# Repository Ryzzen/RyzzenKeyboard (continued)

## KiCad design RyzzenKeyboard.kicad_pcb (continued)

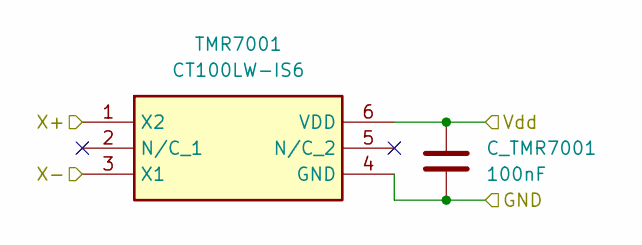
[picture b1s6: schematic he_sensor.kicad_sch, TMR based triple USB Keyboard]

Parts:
C_TMR7001: 100nF; C_0603_1608Metric_Pad1.08x0.95mm_HandSolder
TMR7001: CT100LW-IS6; SOT95P280X135-6N; Mouser Part Number 462-CT100LW-IS6

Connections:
+3.3VA: C_TMR7001.2, TMR7001.6 (VDD); also elsewhere on the board
/keys/key_bank2/S1+: TMR7001.1 (X2); also elsewhere on the board
/keys/key_bank2/S1-: TMR7001.3 (X1); also elsewhere on the board
GND: C_TMR7001.1, TMR7001.4 (GND); also elsewhere on the board

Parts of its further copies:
C_TMR8001, C_TMR9001, C_TMR10001, C_TMR11001, C_TMR12001, C_TMR13001, C_TMR14001, C_TMR15001, C_TMR16001, C_TMR17001, C_TMR18001, C_TMR19001, C_TMR20001, C_TMR21001, C_TMR22001, C_TMR23001, C_TMR24001, C_TMR25001, C_TMR26001, C_TMR27001, C_TMR28001, C_TMR29001, C_TMR30001, C_TMR31001, C_TMR32001, C_TMR33001, C_TMR34001, C_TMR35001, C_TMR36001, C_TMR37001, C_TMR38001: 100nF; C_0603_1608Metric_Pad1.08x0.95mm_HandSolder
TMR8001, TMR9001, TMR10001, TMR11001, TMR12001, TMR13001, TMR14001, TMR15001, TMR16001, TMR17001, TMR18001, TMR19001, TMR20001, TMR21001, TMR22001, TMR23001, TMR24001, TMR25001, TMR26001, TMR27001, TMR28001, TMR29001, TMR30001, TMR31001, TMR32001, TMR33001, TMR34001, TMR35001, TMR36001, TMR37001, TMR38001: CT100LW-IS6; SOT95P280X135-6N; Mouser Part Number 462-CT100LW-IS6

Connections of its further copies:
+3.3VA: C_TMR8001.2, C_TMR9001.2, C_TMR10001.2, C_TMR11001.2, C_TMR12001.2, C_TMR13001.2, C_TMR14001.2, C_TMR15001.2, C_TMR16001.2, C_TMR17001.2, C_TMR18001.2, C_TMR19001.2, C_TMR20001.2, C_TMR21001.2, C_TMR22001.2, C_TMR23001.2, C_TMR24001.2, C_TMR25001.2, C_TMR26001.2, C_TMR27001.2, C_TMR28001.2, C_TMR29001.2, C_TMR30001.2, C_TMR31001.2, C_TMR32001.2, C_TMR33001.2, C_TMR34001.2, C_TMR35001.2, C_TMR36001.2, C_TMR37001.2, C_TMR38001.2, TMR8001.6 (VDD), TMR9001.6 (VDD), TMR10001.6 (VDD), TMR11001.6 (VDD), TMR12001.6 (VDD), TMR13001.6 (VDD), TMR14001.6 (VDD), TMR15001.6 (VDD), TMR16001.6 (VDD), TMR17001.6 (VDD), TMR18001.6 (VDD), TMR19001.6 (VDD), TMR20001.6 (VDD), TMR21001.6 (VDD), TMR22001.6 (VDD), TMR23001.6 (VDD), TMR24001.6 (VDD), TMR25001.6 (VDD), TMR26001.6 (VDD), TMR27001.6 (VDD), TMR28001.6 (VDD), TMR29001.6 (VDD), TMR30001.6 (VDD), TMR31001.6 (VDD), TMR32001.6 (VDD), TMR33001.6 (VDD), TMR34001.6 (VDD), TMR35001.6 (VDD), TMR36001.6 (VDD), TMR37001.6 (VDD), TMR38001.6 (VDD); also elsewhere on the board
/keys/key_bank2/S2+: TMR8001.1 (X2); also elsewhere on the board
/keys/key_bank2/S2-: TMR8001.3 (X1); also elsewhere on the board
/keys/key_bank2/S3+: TMR9001.1 (X2); also elsewhere on the board
/keys/key_bank2/S3-: TMR9001.3 (X1); also elsewhere on the board
/keys/key_bank2/S4+: TMR10001.1 (X2); also elsewhere on the board
/keys/key_bank2/S4-: TMR10001.3 (X1); also elsewhere on the board
/keys/key_bank2/S5+: TMR11001.1 (X2); also elsewhere on the board
/keys/key_bank2/S5-: TMR11001.3 (X1); also elsewhere on the board
/keys/key_bank2/S6+: TMR12001.1 (X2); also elsewhere on the board
/keys/key_bank2/S6-: TMR12001.3 (X1); also elsewhere on the board
/keys/key_bank2/S7+: TMR13001.1 (X2); also elsewhere on the board
/keys/key_bank2/S7-: TMR13001.3 (X1); also elsewhere on the board
/keys/key_bank2/S8+: TMR14001.1 (X2); also elsewhere on the board
/keys/key_bank2/S8-: TMR14001.3 (X1); also elsewhere on the board
/keys/key_bank2/S9+: TMR15001.1 (X2); also elsewhere on the board
/keys/key_bank2/S9-: TMR15001.3 (X1); also elsewhere on the board
/keys/key_bank2/S10+: TMR16001.1 (X2); also elsewhere on the board
/keys/key_bank2/S10-: TMR16001.3 (X1); also elsewhere on the board
/keys/key_bank2/S11+: TMR17001.1 (X2); also elsewhere on the board
/keys/key_bank2/S11-: TMR17001.3 (X1); also elsewhere on the board
/keys/key_bank2/S12+: TMR18001.1 (X2); also elsewhere on the board
/keys/key_bank2/S12-: TMR18001.3 (X1); also elsewhere on the board
/keys/key_bank2/S13+: TMR19001.1 (X2); also elsewhere on the board
/keys/key_bank2/S13-: TMR19001.3 (X1); also elsewhere on the board
/keys/key_bank2/S14+: TMR20001.1 (X2); also elsewhere on the board
/keys/key_bank2/S14-: TMR20001.3 (X1); also elsewhere on the board
/keys/key_bank2/S15+: TMR21001.1 (X2); also elsewhere on the board
/keys/key_bank2/S15-: TMR21001.3 (X1); also elsewhere on the board
/keys/key_bank2/S16+: TMR38001.1 (X2); also elsewhere on the board
/keys/key_bank2/S16-: TMR38001.3 (X1); also elsewhere on the board
/keys/key_bank3/S1+: TMR23001.1 (X2); also elsewhere on the board
/keys/key_bank3/S1-: TMR23001.3 (X1); also elsewhere on the board
/keys/key_bank3/S2+: TMR24001.1 (X2); also elsewhere on the board
/keys/key_bank3/S2-: TMR24001.3 (X1); also elsewhere on the board
/keys/key_bank3/S3+: TMR25001.1 (X2); also elsewhere on the board
/keys/key_bank3/S3-: TMR25001.3 (X1); also elsewhere on the board
/keys/key_bank3/S4+: TMR26001.1 (X2); also elsewhere on the board
/keys/key_bank3/S4-: TMR26001.3 (X1); also elsewhere on the board
/keys/key_bank3/S5+: TMR27001.1 (X2); also elsewhere on the board
/keys/key_bank3/S5-: TMR27001.3 (X1); also elsewhere on the board
/keys/key_bank3/S6+: TMR28001.1 (X2); also elsewhere on the board
/keys/key_bank3/S6-: TMR28001.3 (X1); also elsewhere on the board
/keys/key_bank3/S7+: TMR29001.1 (X2); also elsewhere on the board
/keys/key_bank3/S7-: TMR29001.3 (X1); also elsewhere on the board
/keys/key_bank3/S8+: TMR30001.1 (X2); also elsewhere on the board
/keys/key_bank3/S8-: TMR30001.3 (X1); also elsewhere on the board
/keys/key_bank3/S9+: TMR31001.1 (X2); also elsewhere on the board
/keys/key_bank3/S9-: TMR31001.3 (X1); also elsewhere on the board
/keys/key_bank3/S10+: TMR32001.1 (X2); also elsewhere on the board
/keys/key_bank3/S10-: TMR32001.3 (X1); also elsewhere on the board
/keys/key_bank3/S11+: TMR33001.1 (X2); also elsewhere on the board
/keys/key_bank3/S11-: TMR33001.3 (X1); also elsewhere on the board
/keys/key_bank3/S12+: TMR34001.1 (X2); also elsewhere on the board
/keys/key_bank3/S12-: TMR34001.3 (X1); also elsewhere on the board
/keys/key_bank3/S13+: TMR35001.1 (X2); also elsewhere on the board
/keys/key_bank3/S13-: TMR35001.3 (X1); also elsewhere on the board
/keys/key_bank3/S14+: TMR36001.1 (X2); also elsewhere on the board
/keys/key_bank3/S14-: TMR36001.3 (X1); also elsewhere on the board
/keys/key_bank3/S15+: TMR37001.1 (X2); also elsewhere on the board
/keys/key_bank3/S15-: TMR37001.3 (X1); also elsewhere on the board
/keys/key_bank3/S16+: TMR22001.1 (X2); also elsewhere on the board
/keys/key_bank3/S16-: TMR22001.3 (X1); also elsewhere on the board
GND: C_TMR8001.1, C_TMR9001.1, C_TMR10001.1, C_TMR11001.1, C_TMR12001.1, C_TMR13001.1, C_TMR14001.1, C_TMR15001.1, C_TMR16001.1, C_TMR17001.1, C_TMR18001.1, C_TMR19001.1, C_TMR20001.1, C_TMR21001.1, C_TMR22001.1, C_TMR23001.1, C_TMR24001.1, C_TMR25001.1, C_TMR26001.1, C_TMR27001.1, C_TMR28001.1, C_TMR29001.1, C_TMR30001.1, C_TMR31001.1, C_TMR32001.1, C_TMR33001.1, C_TMR34001.1, C_TMR35001.1, C_TMR36001.1, C_TMR37001.1, C_TMR38001.1, TMR8001.4 (GND), TMR9001.4 (GND), TMR10001.4 (GND), TMR11001.4 (GND), TMR12001.4 (GND), TMR13001.4 (GND), TMR14001.4 (GND), TMR15001.4 (GND), TMR16001.4 (GND), TMR17001.4 (GND), TMR18001.4 (GND), TMR19001.4 (GND), TMR20001.4 (GND), TMR21001.4 (GND), TMR22001.4 (GND), TMR23001.4 (GND), TMR24001.4 (GND), TMR25001.4 (GND), TMR26001.4 (GND), TMR27001.4 (GND), TMR28001.4 (GND), TMR29001.4 (GND), TMR30001.4 (GND), TMR31001.4 (GND), TMR32001.4 (GND), TMR33001.4 (GND), TMR34001.4 (GND), TMR35001.4 (GND), TMR36001.4 (GND), TMR37001.4 (GND), TMR38001.4 (GND); also elsewhere on the board

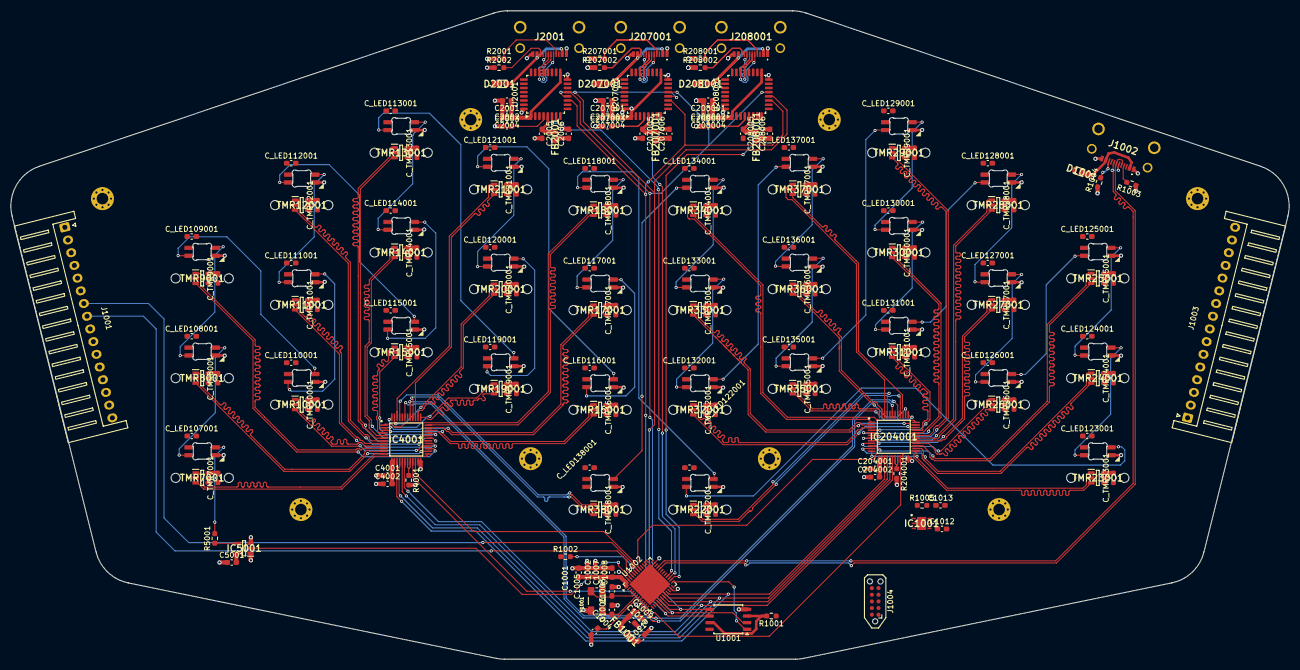
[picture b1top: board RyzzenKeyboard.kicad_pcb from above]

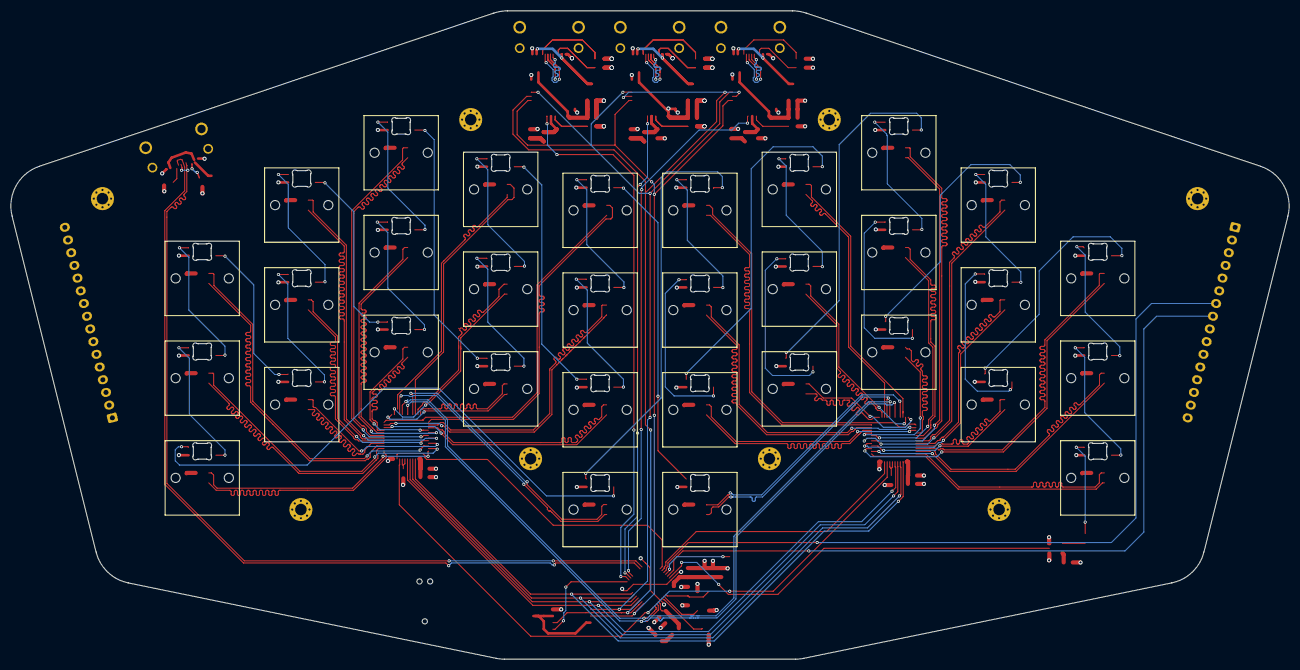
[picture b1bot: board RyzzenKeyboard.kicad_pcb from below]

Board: 4 copper layers, 244.1 x 123.8 mm, 243 parts (160 on the bottom side), 155 nets.

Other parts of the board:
SWITCH1, SWITCH2, SWITCH3, SWITCH4, SWITCH5, SWITCH6, SWITCH7, SWITCH8, SWITCH9, SWITCH10, SWITCH11, SWITCH12, SWITCH13, SWITCH14, SWITCH15, SWITCH16, SWITCH17, SWITCH18, SWITCH19, SWITCH20, SWITCH21, SWITCH22, SWITCH23, SWITCH24, SWITCH25, SWITCH26, SWITCH27, SWITCH28, SWITCH29, SWITCH30, SWITCH31, SWITCH32: SW_Cherry_MX_PCB_Mag_1.00u
_1, _2, _3, _4, _5, _6, _7, _8: MountingHole_2.2mm_M2_Pad_Via

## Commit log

2025-12-15 [ADD](gitingore)
2025-12-15 [ADD](footprint) switches footprint
2025-12-16 [ADD](bank) added first 8 key bank
2025-12-17 [ADD](keys) added keys subsheet
2025-12-20 [ADD](mcu) added decoupling caps, boot reset and crystal
2025-12-22 [ADD](crystal) added values for the crystal's capacitors
2025-12-25 [UPDATE](TMR) switched to TMR sensors + added ldo
2025-12-26 [ADD](HID SPI Bridge)
2025-12-28 [ADD](General) v1
2026-01-02 [ADD](General) v2 split
2026-01-03 [FIX](General) footprints
2026-01-04 [FIX](USB) main usb net labels
2026-01-05 [ADD](General) added all footprints expect leds
2026-01-06 [ADD](General) added all footprints
2026-01-07 [ADD](PCB) outlines
2026-01-07 [ADD](ergogen) footprints
2026-01-07 [UPDATE](PCB) placed LEDs
2026-01-08 [ADD](PCB) led and tmr caps placement
2026-01-09 [ADD](PCB) usbs and uc placement
2026-01-14 [ADD](Mountinghole)
2026-03-23 [ADD](no clue)
2026-04-11 [UPDATE](version 10)
